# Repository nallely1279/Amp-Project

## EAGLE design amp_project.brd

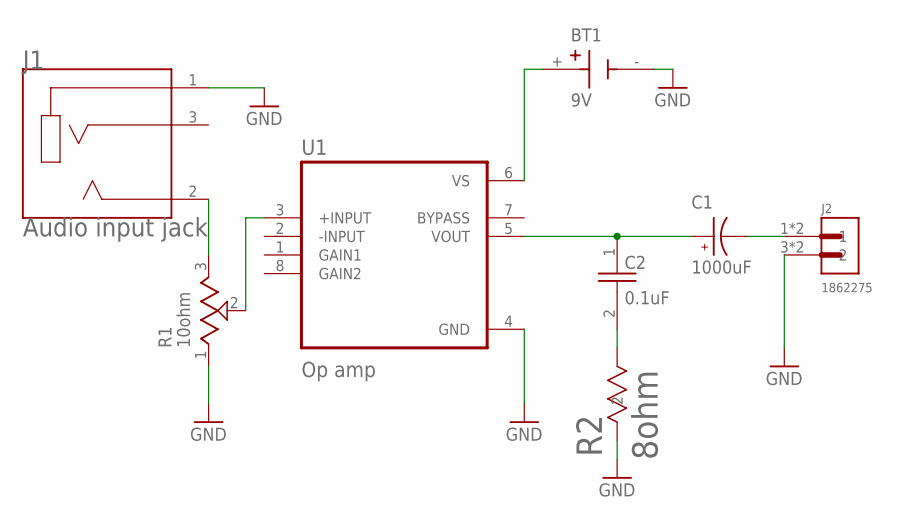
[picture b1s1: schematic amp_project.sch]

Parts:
BT1: 9V; BAT_BH9VPC
C1: 1000uF; CAPPRD500W60D1250H1700
C2: 0.1uF; CAPRR254W51L508T318H635P
J1: Audio input jack; CUI_SJ2-35853A-SMT-TR
J2: 1862275; PHOENIX_1862275
R1: 10ohm; TRIM_3352T-1-103LF
R2: 8ohm; RES_MRS25_VIS
U1: Op amp; DIP794W45P254L959H508Q8

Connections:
GND: BT1.-, J1.1 (SLEEVE), J2.3 (2), J2.4 (2), R1.1 (CCW), R2.2, U1.4 (GND)
unnamed: J1.2 (TIP), R1.3 (CW)
unnamed: R1.2 (WIPER), U1.3 (+INPUT)
unnamed: BT1.+, U1.6 (VS)
unnamed: C1.P, C2.1, U1.5 (VOUT)
unnamed: C1.N, J2.1, J2.2 (1)
unnamed: C2.2, R2.1

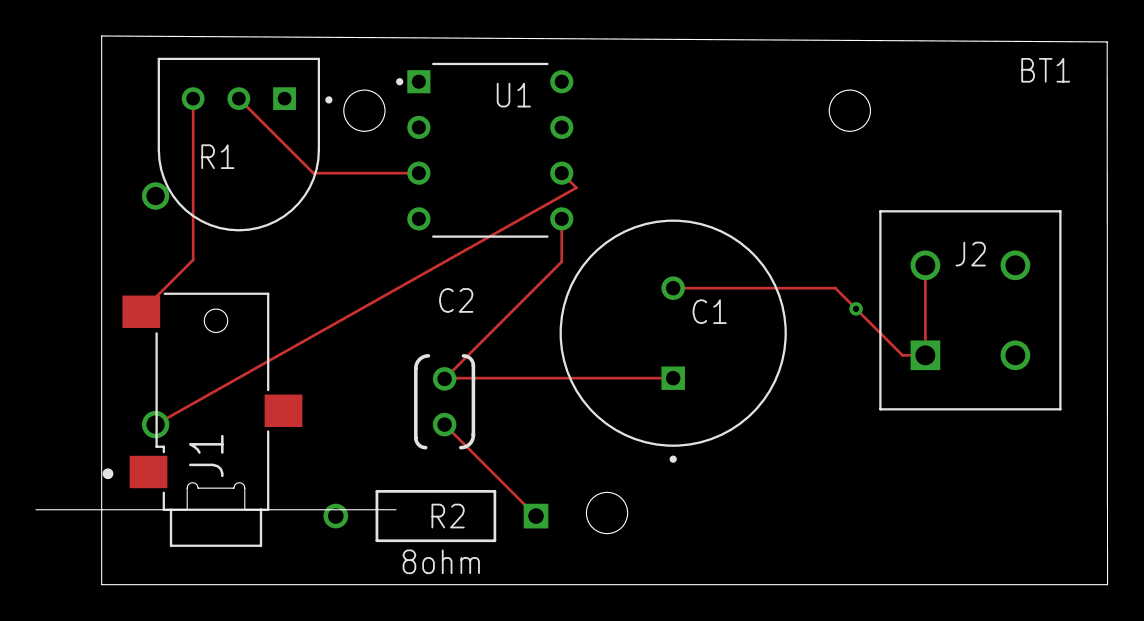
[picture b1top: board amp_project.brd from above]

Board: 2 copper layers, 59.5 x 30.5 mm, 8 parts (1 on the bottom side), 7 nets.
